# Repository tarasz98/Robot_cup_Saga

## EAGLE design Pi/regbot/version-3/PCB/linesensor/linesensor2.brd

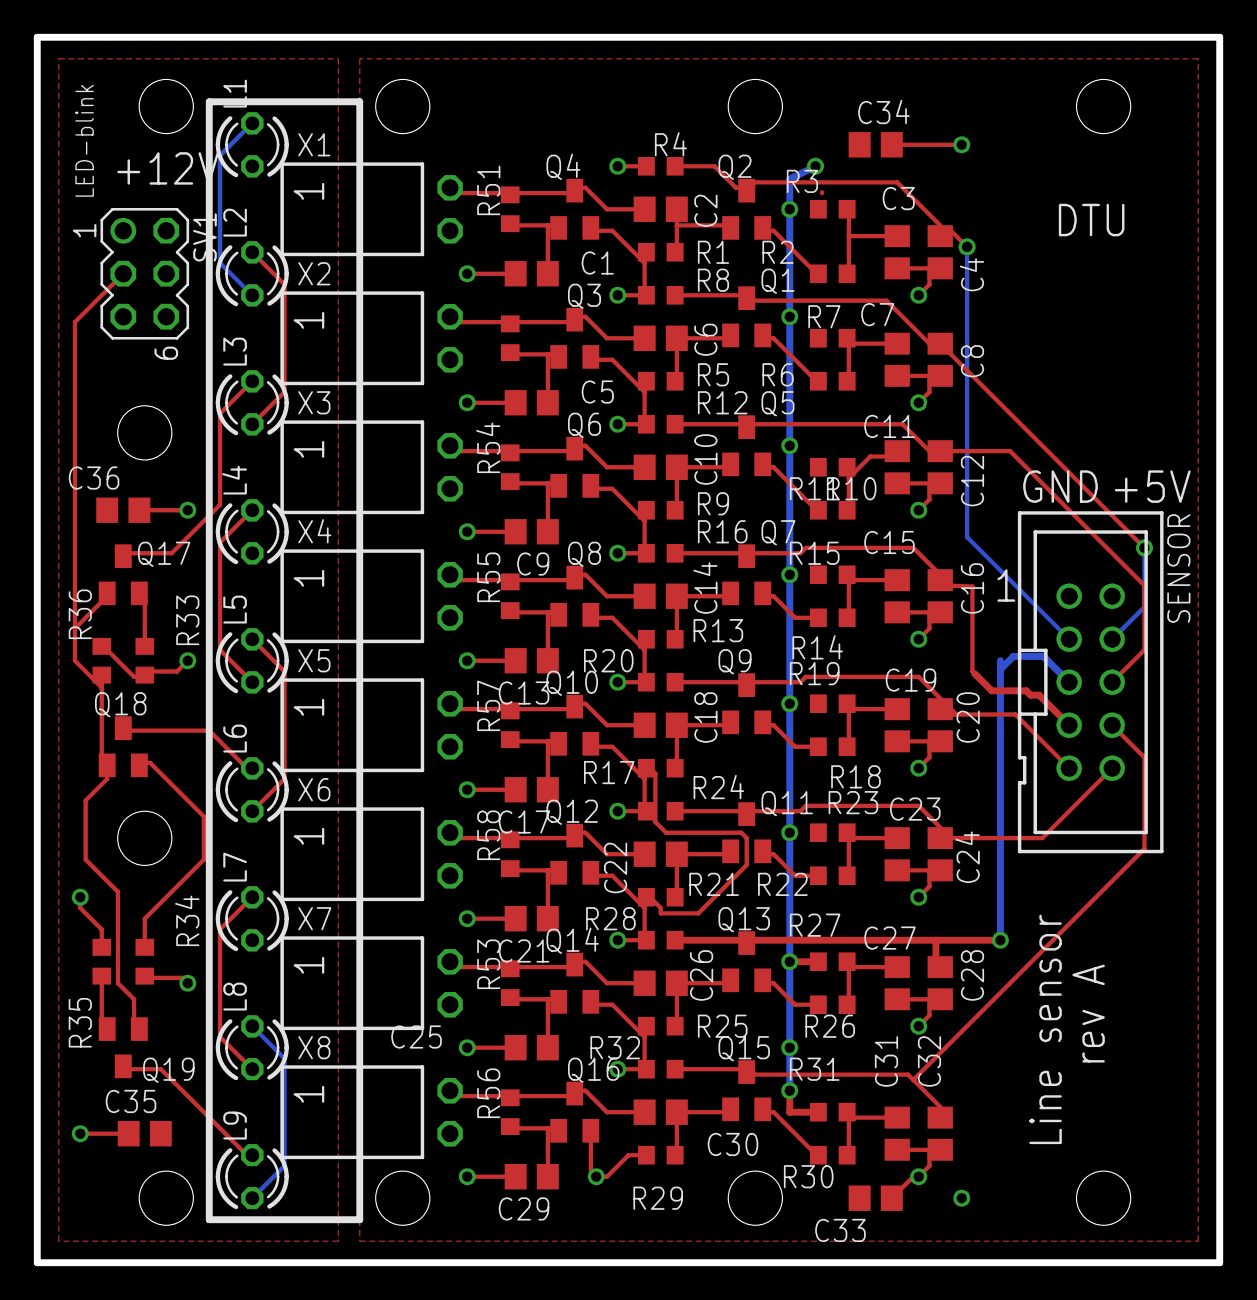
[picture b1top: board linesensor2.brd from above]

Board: 2 copper layers, 69.8 x 72.4 mm, 118 parts (0 on the bottom side), 65 nets.

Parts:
C1, C5, C9, C13, C17, C21, C25, C29: 470nF; C0805
C2, C6, C10, C14, C18, C22, C26, C30: 100pF; C0805
C3, C7, C11, C15, C19, C23, C27, C31, C33, C34, C35, C36: 1uF; C0805
C4, C8, C12, C16, C20, C24, C28, C32: 3.9nF; C0805
L1, L2, L3, L4, L5, L6, L7, L8, L9: red; LED3MM
Q1, Q2, Q3, Q4, Q5, Q6, Q7, Q8, Q9, Q10, Q11, Q12, Q13, Q14, Q15, Q16: SOT23
Q17, Q18, Q19: mmbf170; SOT23
R1, R5, R9, R13, R17, R21, R25, R29: 1M; R0603
R2, R6, R10, R14, R18, R22, R26, R30: 820; R0603
R3, R7, R11, R15, R19, R23, R27, R31: 56k; R0603
R4, R8, R12, R16, R20, R24, R28, R32: 12k; R0603
R33, R34, R35: 12; R0603
R36: 10k; R0603
R51, R52, R53, R54, R55, R56, R57, R58: 820k; R0603
SENSOR: 2510-; PAK100/2500-10
SV1: LEDctrl; MA03-2
X1, X2, X3, X4, X5, X6, X7, X8: SSW-102-02-S-S-RA

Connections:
GATE_CTRL: Q17.1, Q18.1, Q19.1, R36.2, SV1.3
GND: C1.2, C3.1, C4.1, C5.2, C7.1, C8.1, C9.2, C11.1, C12.1, C13.2, C15.1, C16.1, C17.2, C19.1, C20.1, C21.2, C23.1, C24.1, C25.2, C27.1, C28.1, C29.2, C31.1, C32.1, C33.2, C34.2, Q3.2, Q4.2, Q6.2, Q8.2, Q10.2, Q12.2, Q14.2, Q16.2, R1.1, R4.1, R5.1, R8.1, R9.1, R12.1, R13.1, R16.1, R17.1, R20.1, R21.1, R24.1, R25.1, R28.1, R29.1, R32.1, SENSOR.1
GND2: C35.1, C36.1, R33.1, R34.1, R35.1, R36.1, SV1.1
LS0: C4.2, Q2.3, R4.2, SENSOR.3
LS1: C8.2, Q1.3, R8.2, SENSOR.4
LS2: C28.2, Q13.3, R28.2, SENSOR.5
LS3: C12.2, Q5.3, R12.2, SENSOR.6
LS5: C32.2, Q15.3, R32.2, SENSOR.8
LS6: C20.2, Q9.3, R20.2, SENSOR.9
LS7: C24.2, Q11.3, R24.2, SENSOR.10
unnamed: Q2.2, R2.1
unnamed: Q1.2, R6.1
unnamed: C1.1, Q4.1, R51.1
unnamed: C2.1, Q4.3, R51.2, X1.1
unnamed: C2.2, Q2.1, R1.2
unnamed: L1.K, L2.A
unnamed: C3.2, R2.2, R3.1
unnamed: C5.1, Q3.1, R52.1
unnamed: C6.1, Q3.3, R52.2, X2.1
unnamed: C6.2, Q1.1, R5.2
unnamed: L2.K, L3.A
unnamed: C7.2, R6.2, R7.1
unnamed: Q5.2, R10.1
unnamed: C9.1, Q6.1, R54.1
unnamed: C10.1, Q6.3, R54.2, X3.1
unnamed: C10.2, Q5.1, R9.2
unnamed: L4.K, L5.A
unnamed: C11.2, R10.2, R11.1
unnamed: Q7.2, R14.1
unnamed: C13.1, Q8.1, R55.1
unnamed: C14.1, Q8.3, R55.2, X4.1
unnamed: C14.2, Q7.1, R13.2
unnamed: L5.K, L6.A
unnamed: C15.2, R14.2, R15.1
unnamed: Q9.2, R18.1
unnamed: C17.1, Q10.1, R57.1
unnamed: C18.1, Q10.3, R57.2, X5.1
unnamed: C18.2, Q9.1, R17.2
unnamed: L7.K, L8.A
unnamed: C19.2, R18.2, R19.1
unnamed: Q11.2, R22.1
unnamed: C21.1, Q12.1, R58.1
unnamed: C22.1, Q12.3, R58.2, X6.1
unnamed: C22.2, Q11.1, R21.2
unnamed: L8.K, L9.A
unnamed: C23.2, R22.2, R23.1
unnamed: Q13.2, R26.1
unnamed: C25.1, Q14.1, R53.1
unnamed: C26.1, Q14.3, R53.2, X7.1
unnamed: C26.2, Q13.1, R25.2
unnamed: L3.K, Q17.3
unnamed: C27.2, R26.2, R27.1
unnamed: Q15.2, R30.1
unnamed: C29.1, Q16.1, R56.1
unnamed: C30.1, Q16.3, R56.2, X8.1
unnamed: C30.2, Q15.1, R29.2
unnamed: L6.K, Q18.3
unnamed: C31.2, R30.2, R31.1
unnamed: L9.K, Q19.3
unnamed: Q17.2, R33.2
unnamed: Q18.2, R34.2
unnamed: Q19.2, R35.2
unnamed: C16.2, Q7.3, R16.2, SENSOR.7
VDD: C33.1, C34.1, R3.2, R7.2, R11.2, R15.2, R19.2, R23.2, R27.2, R31.2, SENSOR.2, X1.2, X2.2, X3.2, X4.2, X5.2, X6.2, X7.2, X8.2
VDD2: C35.2, C36.2, L1.A, L4.A, L7.A, SV1.2

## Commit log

2022-03-02 Copied all data from pi
2022-03-02 Updated file structure
2022-03-03 test
2022-03-04 Just a test push
2022-03-04 Another push
